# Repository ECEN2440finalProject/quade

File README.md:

# quade
ECEN 2440 quade code

Repository for RC Quade (Quadruped robot with MSP432 as its base, controlled wirelessly by a remote control with joystick).

ECEN 2440 Final Project Team 11 - Michael L, Terry V, Wyatt S, Ethan C

Fall, 2020

All code files (original and leveraged) can be found here, along with:
  - Texas Instruments MSP432P401R LaunchPad datasheet, header file, and Technical Reference Manual (quade/Datasheet_TechRefMan/)
  - EAGLE PCB schematic and board design files for Arduino Uno shield, for remote control (quade/Arduino_Uno_Shield/)

Works Cited/Leveraged Code:
  - Tyler Davidson: IMU_TestBench code (stIMU.c/.h, pca9685.c/.h, i2c.c/.h, parts of main.c); FirstSteps code (servo.c/.h, parts of gait.c/.h)
  - Paul Stoffregen: RadioHead library (basis of our custom Arduino sketch for RF Link Transmitter)
    - https://github.com/PaulStoffregen/RadioHead
  - Texas Instruments, Inc: MSP432 Driver Library (used for ADC code)
    - adc14.c/.h, cpu.c/.h, debug.h, gpio.c/.h, interrupt.c/.h, sysctl.c/.h, sysctl_a.c/.h
    - https://software-dl.ti.com/msp430/msp430_public_sw/mcu/msp430/MSP432_Driver_Library/latest/index_FDS.html

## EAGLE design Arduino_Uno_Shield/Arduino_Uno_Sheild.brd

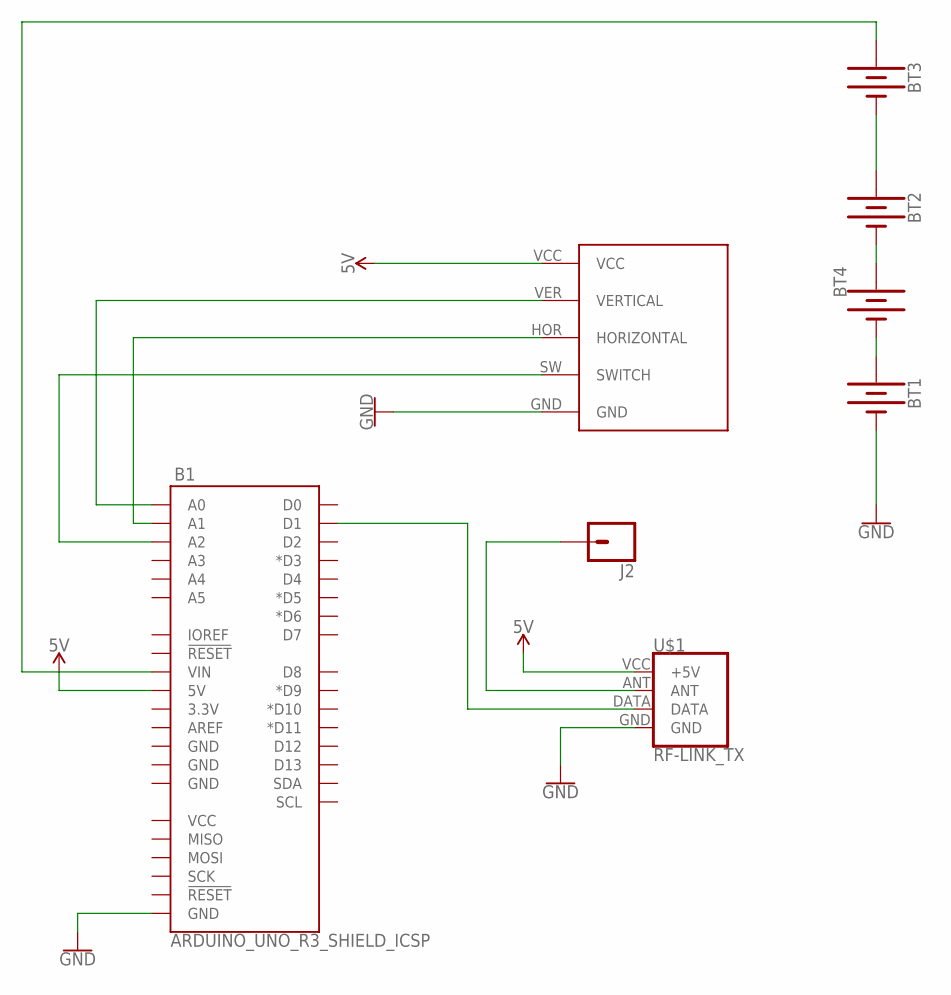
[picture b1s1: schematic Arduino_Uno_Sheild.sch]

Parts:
B1: ARDUINO_UNO_R3_SHIELD_ICSP; UNO_R3_SHIELD_ICSP
BT1, BT2, BT3, BT4: BATTERY-AAA
J2: CONN_01POGOPIN_HOLE_0.58; 1X01_POGOPIN_HOLE_0.58_DIA
JOYSTICK1: JOYSTICK
U$1: RF-LINK_TX

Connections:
5V: B1.5V, JOYSTICK1.VCC, U$1.VCC (+5V)
GND: B1.GND_ICSP (GND), BT1.GND@1 (-), JOYSTICK1.GND, U$1.GND
unnamed: B1.TX (D1), U$1.DATA
unnamed: J2.1, U$1.ANT
unnamed: B1.A0, JOYSTICK1.VER (VERTICAL)
unnamed: B1.A1, JOYSTICK1.HOR (HORIZONTAL)
unnamed: B1.A2, JOYSTICK1.SW (SWITCH)
unnamed: B1.VIN, BT3.PWR@1 (+)
unnamed: BT2.PWR@1 (+), BT3.GND@1 (-)
unnamed: BT2.GND@1 (-), BT4.PWR@1 (+)
unnamed: BT1.PWR@1 (+), BT4.GND@1 (-)

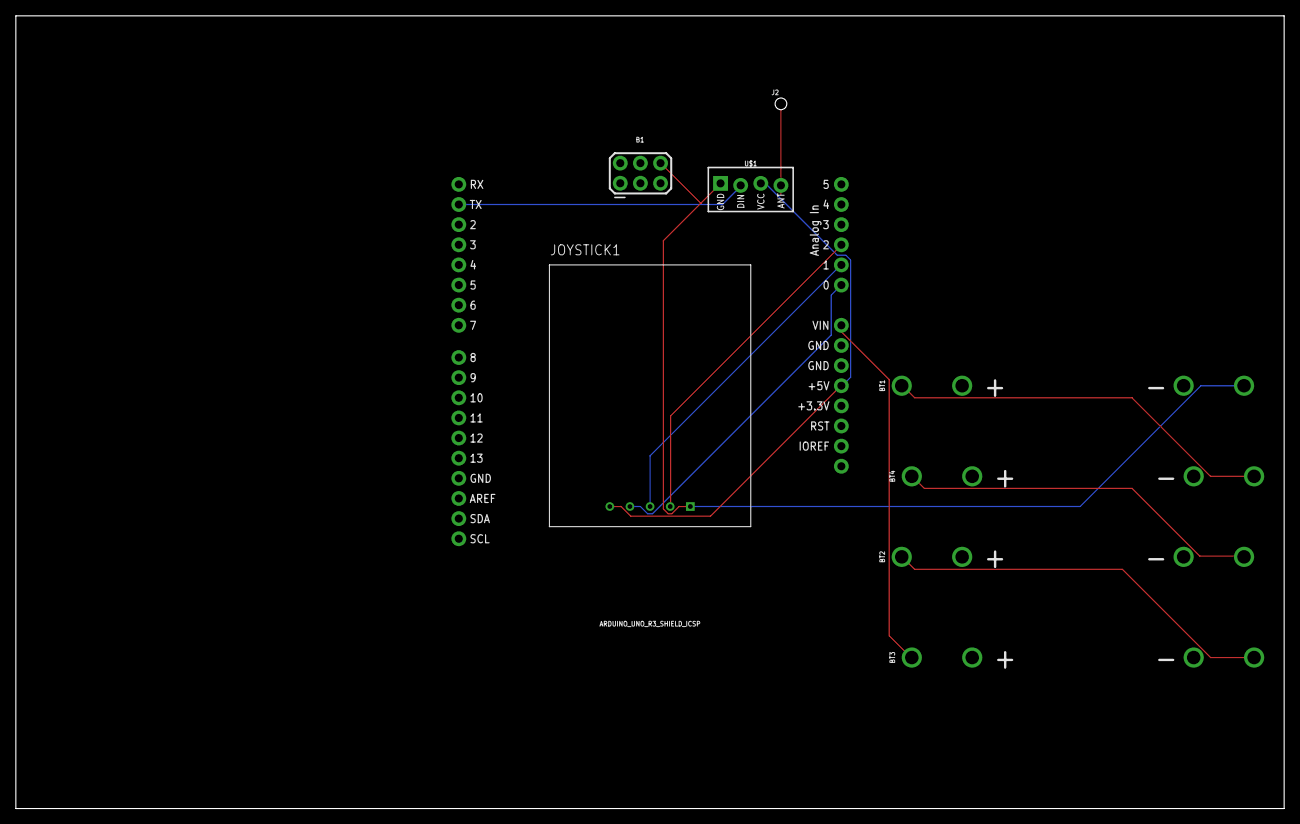
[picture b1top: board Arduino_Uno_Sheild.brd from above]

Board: 2 copper layers, 160.0 x 100.0 mm, 8 parts (0 on the bottom side), 11 nets.

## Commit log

2020-10-26 Update transmitter_ECEN2440.ino
    Ok this works now, I tested on waveforms and confirmed values
2020-11-11 Add files via upload
    EUSCI_A3 interrupt handler is in here (not in uart.c) and I previously had the wrong interrupt handler (for EUSCI_A0)

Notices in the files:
parts and their libraries:
SparkFun-Boards: Licensing: Creative Commons ShareAlike 4.0 International - https://creativecommons.org/licenses/by-sa/4.0
